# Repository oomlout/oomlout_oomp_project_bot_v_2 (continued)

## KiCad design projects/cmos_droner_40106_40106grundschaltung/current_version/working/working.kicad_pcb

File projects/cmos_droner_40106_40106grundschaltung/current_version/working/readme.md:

# 40106
 
## summary 
* id: cmos_droner_40106_40106grundschaltung
* user: cmos_droner
* name: 40106
* board: 40106grundschaltung
* repo: https://github.com/cmos-droner/40106
* src_file_repo_kicad_pcb: core/40106grundschaltung.kicad_pcb
* src_file_repo_kicad_pcb_link: https://github.com/cmos-droner/40106/tree/master/core/40106grundschaltung.kicad_pcb

* src_file_repo_sch: core/40106grundschaltung.sch
* src_file_repo_sch_link: https://github.com/cmos-droner/40106/tree/master/core/40106grundschaltung.sch
* full details link: https://github.com/oomlout/oomlout_oomp_project_bot_v_2/tree/main/projects/cmos_droner_40106_40106grundschaltung/current_version/working

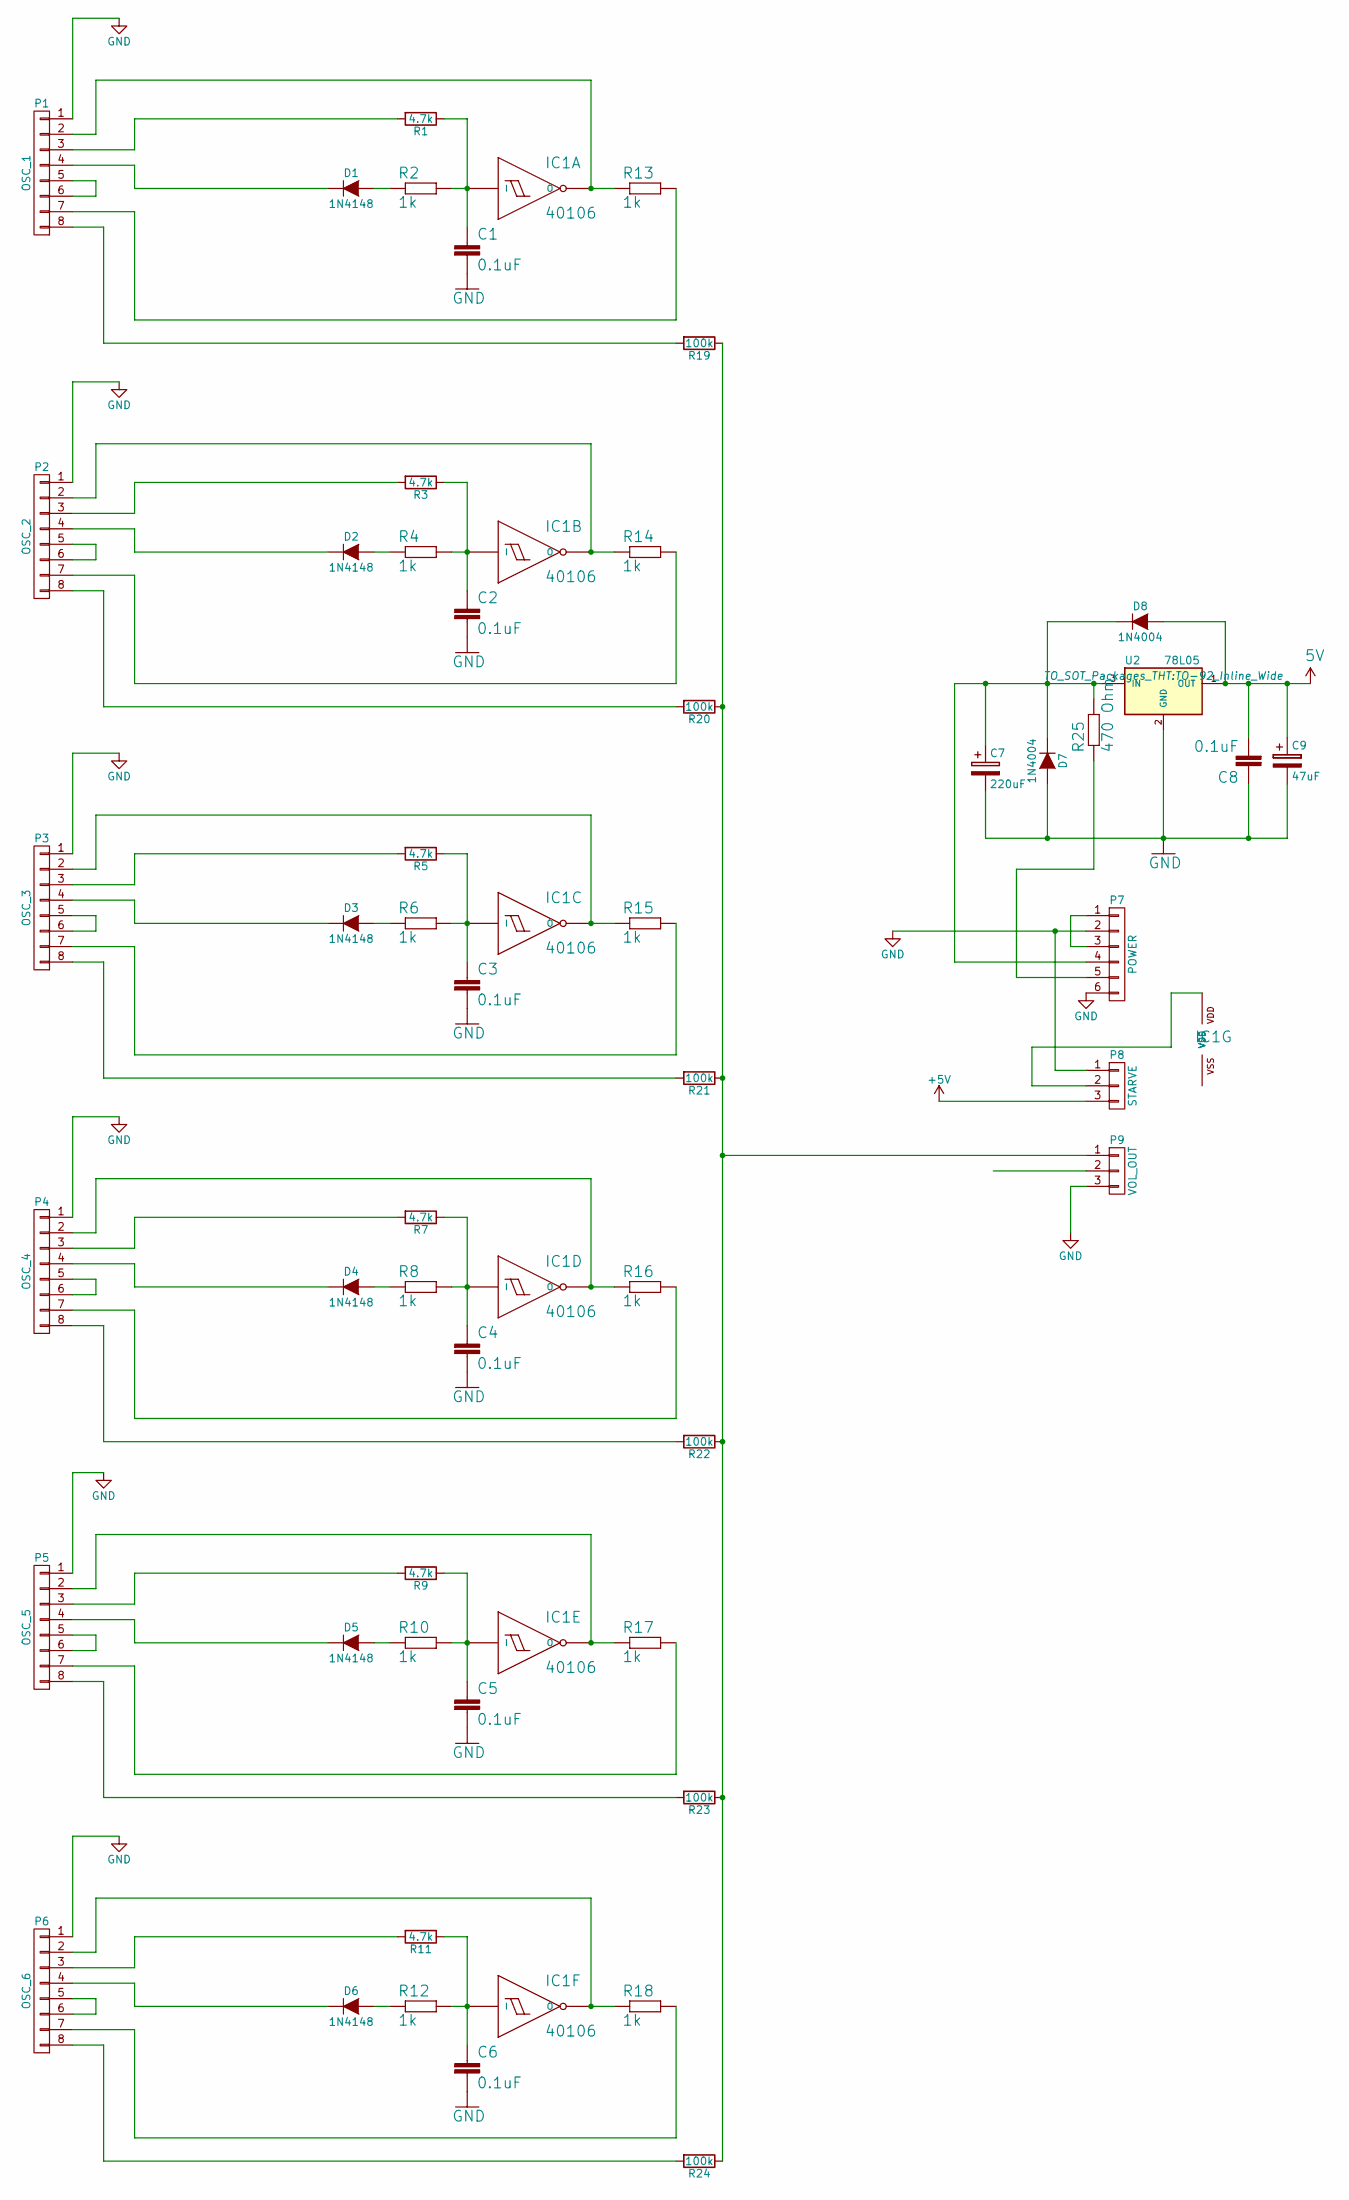
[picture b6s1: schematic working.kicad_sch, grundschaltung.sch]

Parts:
C1, C2, C3, C4, C5, C6, C8: 0.1uF; C_Rect_L4.5_W2.5_P3
C7: 220uF; C_Radial_D7.5_L11.2_P2.5
C9: 47uF; C_Radial_D5_L11_P2.5
D1, D2, D3, D4, D5, D6: 1N4148; Diode_DO-35_SOD27_Horizontal_RM10
D7, D8: 1N4004; Diode_DO-41_SOD81_Horizontal_RM10
IC1: 40106; DIP-14_W7.62mm_LongPads
P1: OSC_1; Pin_Header_Straight_1x08
P2: OSC_2; Pin_Header_Straight_1x08
P3: OSC_3; Pin_Header_Straight_1x08
P4: OSC_4; Pin_Header_Straight_1x08
P5: OSC_5; Pin_Header_Straight_1x08
P6: OSC_6; Pin_Header_Straight_1x08
P7: POWER; Pin_Header_Straight_1x06
P8: STARVE; Pin_Header_Straight_1x03
P9: VOL_OUT; Pin_Header_Straight_1x03
R1, R3, R5, R7, R9, R11: 4.7k; Resistor_Horizontal_RM7mm_Wide
R2, R4, R6, R8, R10, R12, R13, R14, R15, R16, R17, R18: 1k; Resistor_Horizontal_RM7mm_Wide
R19, R20, R21, R22, R23, R24: 100k; Resistor_Horizontal_RM7mm_Wide
R25: 470 Ohm; Resistor_Horizontal_RM7mm_Wide
U2: 78L05; TO-92_Inline_Wide

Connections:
5V: C8.2, C9.1, D8.2 (A), U2.1 (OUT)
GND: C1.2, C2.2, C3.2, C4.2, C5.2, C6.2, C7.2, C8.1, C9.2, D7.2 (A), P1.1, P2.1, P3.1, P4.1, P5.1, P6.1, P7.2, P7.6, P8.1, P9.3, U2.2 (GND)
unnamed: C1.1, IC1.1 (I), R1.1, R2.2
unnamed: C2.1, IC1.3 (I), R3.1, R4.2
unnamed: C3.1, IC1.5 (I), R5.1, R6.2
unnamed: C4.1, IC1.9 (I), R7.1, R8.2
unnamed: C5.1, IC1.11 (I), R9.1, R10.2
unnamed: C6.1, IC1.13 (I), R11.1, R12.2
unnamed: C7.1, D7.1 (K), D8.1 (K), P7.4, R25.2, U2.3 (IN)
unnamed: D1.1 (K), P1.4
unnamed: D1.2 (A), R2.1
unnamed: D2.1 (K), P2.4
unnamed: D2.2 (A), R4.1
unnamed: D3.1 (K), P3.4
unnamed: D3.2 (A), R6.1
unnamed: D4.1 (K), P4.4
unnamed: D4.2 (A), R8.1
unnamed: D5.1 (K), P5.4
unnamed: D5.2 (A), R10.1
unnamed: D6.1 (K), P6.4
unnamed: D6.2 (A), R12.1
unnamed: IC1.2 (O), P1.2, R13.1
unnamed: IC1.4 (O), P2.2, R14.1
unnamed: IC1.6 (O), P3.2, R15.1
unnamed: IC1.8 (O), P4.2, R16.1
unnamed: IC1.10 (O), P5.2, R17.1
unnamed: IC1.12 (O), P6.2, R18.1
unnamed: IC1.14 (VDD), P8.2
unnamed: P1.3, R1.2
unnamed: P1.5, P1.6
unnamed: P1.7, R13.2
unnamed: P1.8, R19.2
unnamed: P2.3, R3.2
unnamed: P2.5, P2.6
unnamed: P2.7, R14.2
unnamed: P2.8, R20.2
unnamed: P3.3, R5.2
unnamed: P3.5, P3.6
unnamed: P3.7, R15.2
unnamed: P3.8, R21.2
unnamed: P4.3, R7.2
unnamed: P4.5, P4.6
unnamed: P4.7, R16.2
unnamed: P4.8, R22.2
unnamed: P5.3, R9.2
unnamed: P5.5, P5.6
unnamed: P5.7, R17.2
unnamed: P5.8, R23.2
unnamed: P6.3, R11.2
unnamed: P6.5, P6.6
unnamed: P6.7, R18.2
unnamed: P6.8, R24.2
unnamed: P7.1, P7.3
unnamed: P7.5, R25.1
unnamed: P9.1, R19.1, R20.1, R21.1, R22.1, R23.1, R24.1

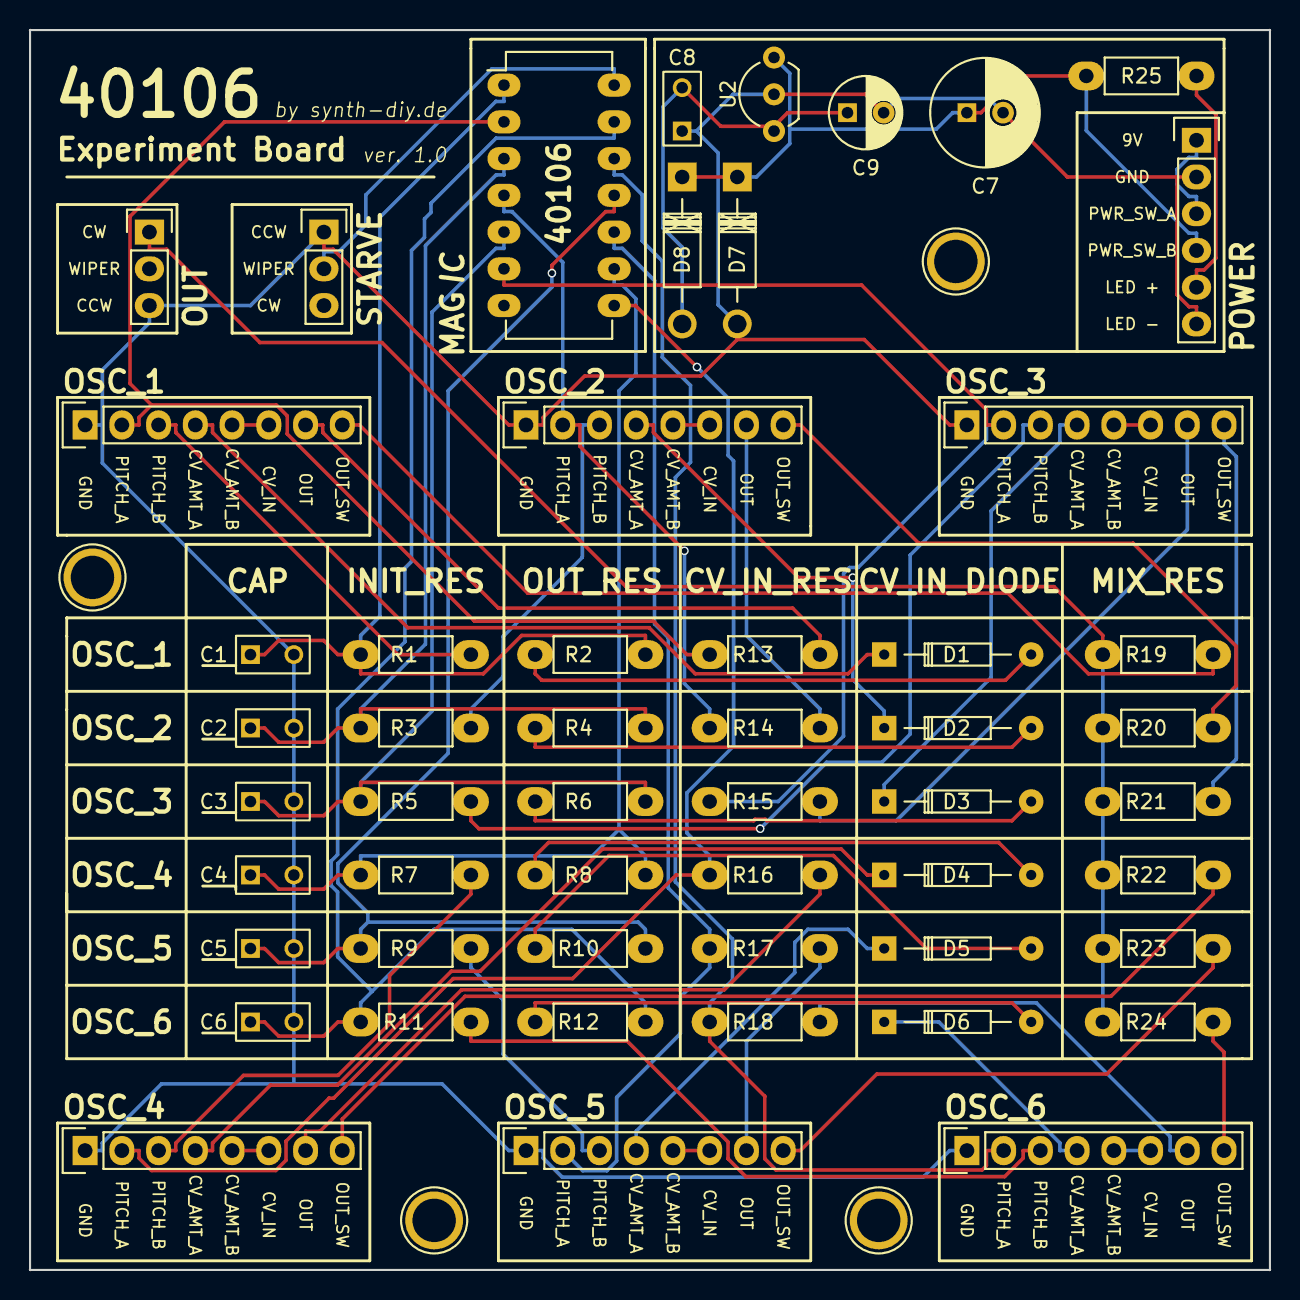
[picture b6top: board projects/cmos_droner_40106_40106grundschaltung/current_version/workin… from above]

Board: 2 copper layers, 85.7 x 85.7 mm, 57 parts (0 on the bottom side), 55 nets.

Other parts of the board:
H1, H2, H3, H4: 1pin

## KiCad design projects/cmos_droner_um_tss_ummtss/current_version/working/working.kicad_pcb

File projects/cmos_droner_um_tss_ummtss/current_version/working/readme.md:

# um_tss
 
## summary 
* id: cmos_droner_um_tss_ummtss
* user: cmos_droner
* name: um_tss
* board: ummtss
* repo: https://github.com/cmos-droner/UM-TSS
* src_file_repo_kicad_pcb: schematics v2/front/ummtss.kicad_pcb
* src_file_repo_kicad_pcb_link: https://github.com/cmos-droner/UM-TSS/tree/master/schematics v2/front/ummtss.kicad_pcb

* src_file_repo_sch: schematics v2/front/ummtss.sch
* src_file_repo_sch_link: https://github.com/cmos-droner/UM-TSS/tree/master/schematics v2/front/ummtss.sch
* full details link: https://github.com/oomlout/oomlout_oomp_project_bot_v_2/tree/main/projects/cmos_droner_um_tss_ummtss/current_version/working

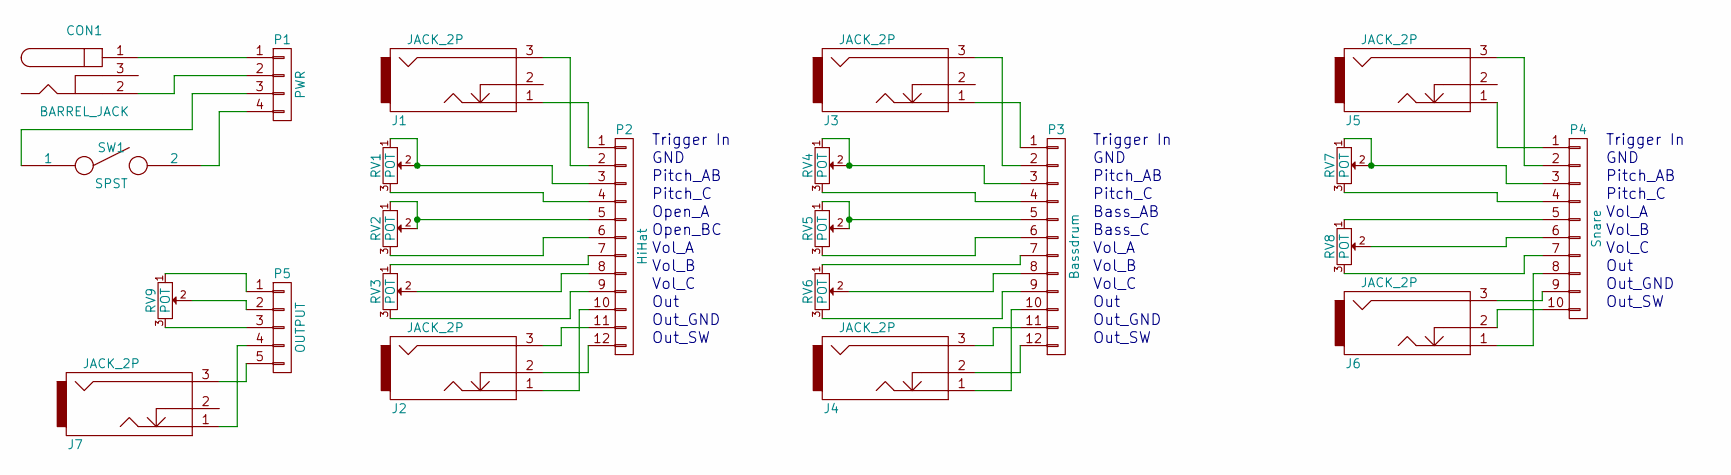
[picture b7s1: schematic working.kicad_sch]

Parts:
CON1: BARREL_JACK
J1, J2, J3, J4, J5, J6, J7: JACK_2P; jack-PJ301M
P1: PWR; Pin_Header_Straight_1x04
P2: HiHat; Pin_Header_Straight_1x12
P3: Bassdrum; Pin_Header_Straight_1x12
P4: Snare; Pin_Header_Straight_1x10
P5: OUTPUT; Pin_Header_Straight_1x05
RV1, RV2, RV3, RV4, RV5, RV6, RV7, RV8, RV9: POT; pot_alpha-9mm--vertical
SW1: SPST; SW_Micro_SPST

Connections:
unnamed: CON1.1, P1.1
unnamed: CON1.2, P1.2
unnamed: J1.1, P2.1
unnamed: J1.3, P2.2
unnamed: J2.1, P2.10
unnamed: J2.2, P2.12
unnamed: J2.3, P2.11
unnamed: J3.1, P3.1
unnamed: J3.3, P3.2
unnamed: J4.1, P3.10
unnamed: J4.2, P3.12
unnamed: J4.3, P3.11
unnamed: J5.1, P4.1
unnamed: J5.3, P4.2
unnamed: J6.1, P4.8
unnamed: J6.2, P4.10
unnamed: J6.3, P4.9
unnamed: J7.1, P5.4
unnamed: J7.3, P5.5
unnamed: P1.3, SW1.1
unnamed: P1.4, SW1.2
unnamed: P2.3, RV1.1, RV1.2
unnamed: P2.4, RV1.3
unnamed: P2.5, RV2.1, RV2.2
unnamed: P2.6, RV2.3
unnamed: P2.7, RV3.1
unnamed: P2.8, RV3.2
unnamed: P2.9, RV3.3
unnamed: P3.3, RV4.1, RV4.2
unnamed: P3.4, RV4.3
unnamed: P3.5, RV5.1, RV5.2
unnamed: P3.6, RV5.3
unnamed: P3.7, RV6.1
unnamed: P3.8, RV6.2
unnamed: P3.9, RV6.3
unnamed: P4.3, RV7.1, RV7.2
unnamed: P4.4, RV7.3
unnamed: P4.5, RV8.1
unnamed: P4.6, RV8.2
unnamed: P4.7, RV8.3
unnamed: P5.1, RV9.1
unnamed: P5.2, RV9.2
unnamed: P5.3, RV9.3

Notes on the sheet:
Pitch_AB
Out_SW
Bass_AB
Vol_A
Vol_C
Out
Trigger In
Out_GND
Pitch_C
Vol_B
GND
Open_BC
Open_A
Bass_C

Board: 2 copper layers, 23 parts (0 on the bottom side), 43 nets, no tracks yet.
